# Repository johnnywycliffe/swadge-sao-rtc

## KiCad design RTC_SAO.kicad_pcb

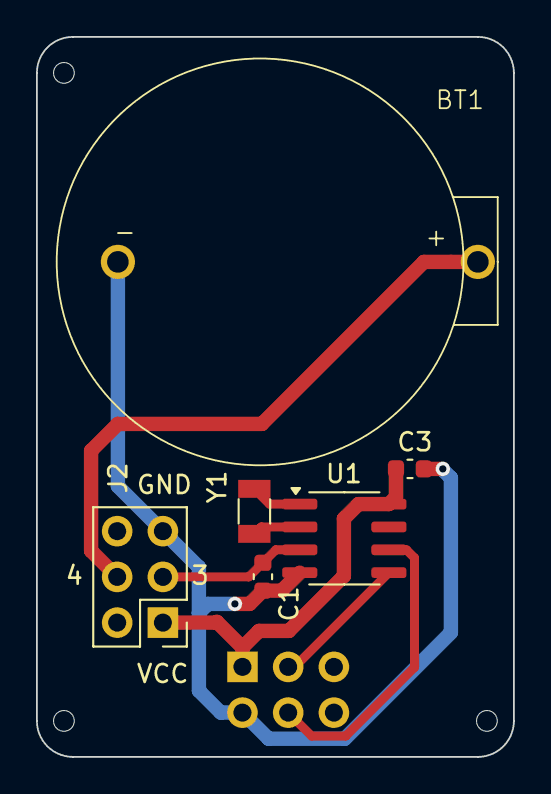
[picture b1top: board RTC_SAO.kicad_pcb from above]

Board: 2 copper layers, 26.5 x 40.0 mm, 10 parts (1 on the bottom side), 8 nets.

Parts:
BT1: Battery_Cell; BS-02-A1AK010
C1, C3: 100nF; C_0603_1608Metric
H1, H2, H3: tooling_hole
J1: SAO Header; PinHeader_2x03_P2.54mm_Vertical
J2: Testing header; PinHeader_2x03_P2.54mm_Vertical
U1: DS1307Z+; SOIC-8_3.9x4.9mm_P1.27mm
Y1: 32.768kHz; Crystal_SMD_3215-2Pin_3.2x1.5mm

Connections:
/SCL: J1.4 (SCL), U1.6 (SCL)
/SDA: J1.3 (SDA), U1.5 (SDA)
GND: BT1.2 (-), C1.2, C3.2, J1.2 (GND), J2.5, U1.4 (GND)
unnamed: BT1.1 (+), J2.4
unnamed: C1.1, J2.3, U1.3 (VBAT)
unnamed: U1.1 (X1), Y1.2
unnamed: U1.2 (X2), Y1.1
VCC: C3.1, J1.1 (VCC), J2.1, U1.8 (VCC)
